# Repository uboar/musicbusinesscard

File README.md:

# musicbusinesscard
 
詳細→https://uboar.hatenablog.com/entry/2020/05/02/111120

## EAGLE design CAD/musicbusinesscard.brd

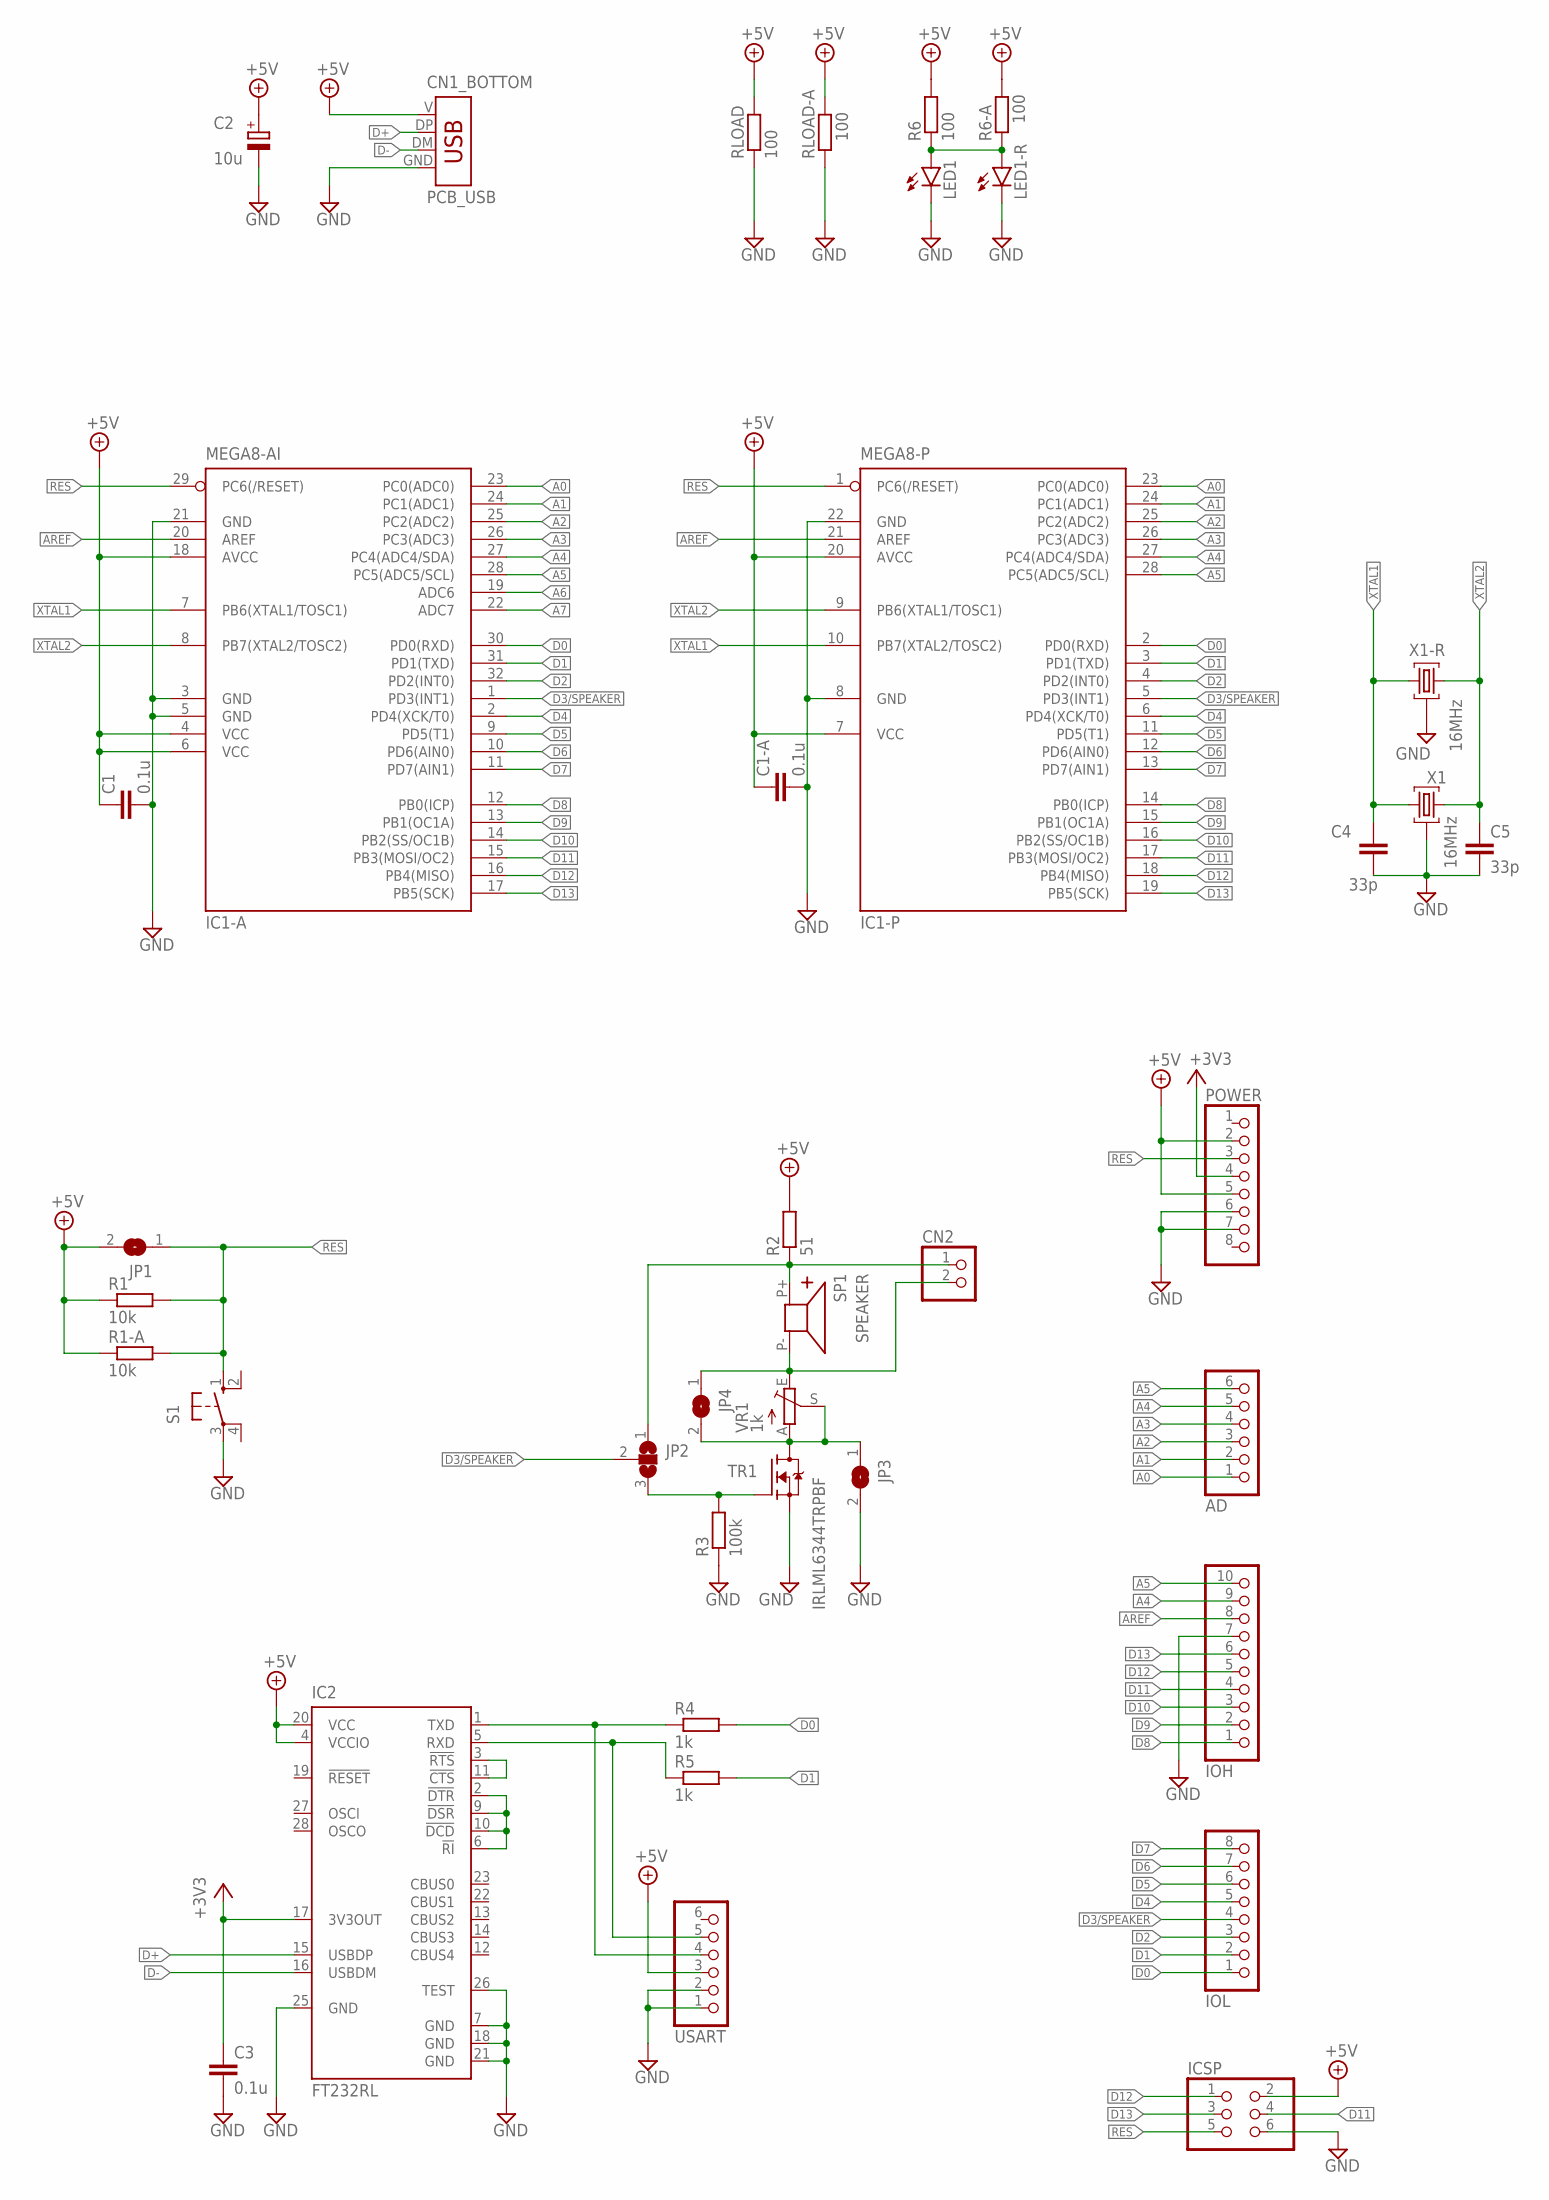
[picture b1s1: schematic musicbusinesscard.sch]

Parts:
AD: PINHD-1X6; 1X06
C1, C3: 0.1u; C3216
C1-A: 0.1u; C050-024X044
C2: 10u; TT2D5
C4, C5: 33p; C050-024X044
CN1_BOTTOM: PCB_USB
CN2: PINHD-1X2; 1X02
IC1-A: MEGA8-AI; TQFP32-08
IC1-P: MEGA8-P; DIL28-3
IC2: FT232RL; SSOP28
ICSP: PINHD-2X3; 2X03
IOH: PINHD-1X10; 1X10
IOL: PINHD-1X8; 1X08
JP1, JP3, JP4: SJ
JP2: SJ2W; SJ_2
LED1: LEDCHIPLED_1206; CHIPLED_1206
LED1-R: LED3MM
POWER: PINHD-1X8; 1X08
R1: 10k; R3216
R1-A: 10k; 0207/10
R2: 51; R3216
R3: 100k; R3216
R4, R5: 1k; R3216
R6: 100; R3216
R6-A: 100; 0207/10
RLOAD: 100; R3216
RLOAD-A: 100; 0207/10
S1: 10-XX; B3F-10XX
SP1: SPEAKER
TR1: IRLML6344TRPBF; SOT23
USART: PINHD-1X6; 1X06
VR1: 1k; B25P
X1: 16MHz; XTAL_MURATA
X1-R: 16MHz; HC49U

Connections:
+3V3: C3.1, IC2.17 (3V3OUT), POWER.4
+5V: C1.1, C1-A.1, C2.+, CN1_BOTTOM.V (1), IC1-A.4 (VCC), IC1-A.6 (VCC), IC1-A.18 (AVCC), IC1-P.7 (VCC), IC1-P.20 (AVCC), IC2.4 (VCCIO), IC2.20 (VCC), ICSP.2, JP1.2, POWER.2, POWER.5, R1.1, R1-A.1, R2.2, R6.2, R6-A.2, RLOAD.2, RLOAD-A.2, USART.3
A0: AD.1, IC1-A.23 (PC0(ADC0)), IC1-P.23 (PC0(ADC0))
A1: AD.2, IC1-A.24 (PC1(ADC1)), IC1-P.24 (PC1(ADC1))
A2: AD.3, IC1-A.25 (PC2(ADC2)), IC1-P.25 (PC2(ADC2))
A3: AD.4, IC1-A.26 (PC3(ADC3)), IC1-P.26 (PC3(ADC3))
A4: AD.5, IC1-A.27 (PC4(ADC4/SDA)), IC1-P.27 (PC4(ADC4/SDA)), IOH.9
A5: AD.6, IC1-A.28 (PC5(ADC5/SCL)), IC1-P.28 (PC5(ADC5/SCL)), IOH.10
A6: IC1-A.19 (ADC6)
A7: IC1-A.22 (ADC7)
AREF: IC1-A.20 (AREF), IC1-P.21 (AREF), IOH.8
D0: IC1-A.30 (PD0(RXD)), IC1-P.2 (PD0(RXD)), IOL.1, R4.2
D1: IC1-A.31 (PD1(TXD)), IC1-P.3 (PD1(TXD)), IOL.2, R5.2
D2: IC1-A.32 (PD2(INT0)), IC1-P.4 (PD2(INT0)), IOL.3
D3/SPEAKER: IC1-A.1 (PD3(INT1)), IC1-P.5 (PD3(INT1)), IOL.4, JP2.2
D4: IC1-A.2 (PD4(XCK/T0)), IC1-P.6 (PD4(XCK/T0)), IOL.5
D5: IC1-A.9 (PD5(T1)), IC1-P.11 (PD5(T1)), IOL.6
D6: IC1-A.10 (PD6(AIN0)), IC1-P.12 (PD6(AIN0)), IOL.7
D7: IC1-A.11 (PD7(AIN1)), IC1-P.13 (PD7(AIN1)), IOL.8
D8: IC1-A.12 (PB0(ICP)), IC1-P.14 (PB0(ICP)), IOH.1
D9: IC1-A.13 (PB1(OC1A)), IC1-P.15 (PB1(OC1A)), IOH.2
D10: IC1-A.14 (PB2(SS/OC1B)), IC1-P.16 (PB2(SS/OC1B)), IOH.3
D11: IC1-A.15 (PB3(MOSI/OC2)), IC1-P.17 (PB3(MOSI/OC2)), ICSP.4, IOH.4
D12: IC1-A.16 (PB4(MISO)), IC1-P.18 (PB4(MISO)), ICSP.1, IOH.5
D13: IC1-A.17 (PB5(SCK)), IC1-P.19 (PB5(SCK)), ICSP.3, IOH.6
D+: CN1_BOTTOM.DP (2), IC2.15 (USBDP)
D-: CN1_BOTTOM.DM (3), IC2.16 (USBDM)
GND: C1.2, C1-A.2, C2.-, C3.2, C4.2, C5.2, CN1_BOTTOM.GND (4), IC1-A.3 (GND), IC1-A.5 (GND), IC1-A.21 (GND), IC1-P.8 (GND), IC1-P.22 (GND), IC2.7 (GND), IC2.18 (GND), IC2.21 (GND), IC2.25 (GND), IC2.26 (TEST), ICSP.6, IOH.7, JP3.2, LED1.C, LED1-R.K (C), POWER.6, POWER.7, R3.1, RLOAD.1, RLOAD-A.1, S1.3, TR1.2 (S), USART.1, USART.2, X1.2, X1-R.2
unnamed: JP2.3, R3.2, TR1.1 (G)
unnamed: CN2.2, JP4.1, SP1.P- (2), VR1.E
unnamed: CN2.1, JP2.1, R2.1, SP1.P+ (1)
unnamed: JP3.1, JP4.2, TR1.3 (D), VR1.A, VR1.S
unnamed: IC2.2 (!DTR), IC2.6 (!RI), IC2.9 (!DSR), IC2.10 (!DCD)
unnamed: IC2.3 (!RTS), IC2.11 (!CTS)
unnamed: IC2.1 (TXD), R4.1, USART.4
unnamed: IC2.5 (RXD), R5.1, USART.5
unnamed: LED1.A, LED1-R.A, R6.1, R6-A.1
RES: IC1-A.29 (PC6(/RESET)), IC1-P.1 (PC6(/RESET)), ICSP.5, JP1.1, POWER.3, R1.2, R1-A.2, S1.1 (S)
XTAL1: C4.1, IC1-A.7 (PB6(XTAL1/TOSC1)), IC1-P.10 (PB7(XTAL2/TOSC2)), X1.1, X1-R.1
XTAL2: C5.1, IC1-A.8 (PB7(XTAL2/TOSC2)), IC1-P.9 (PB6(XTAL1/TOSC1)), X1.3, X1-R.3

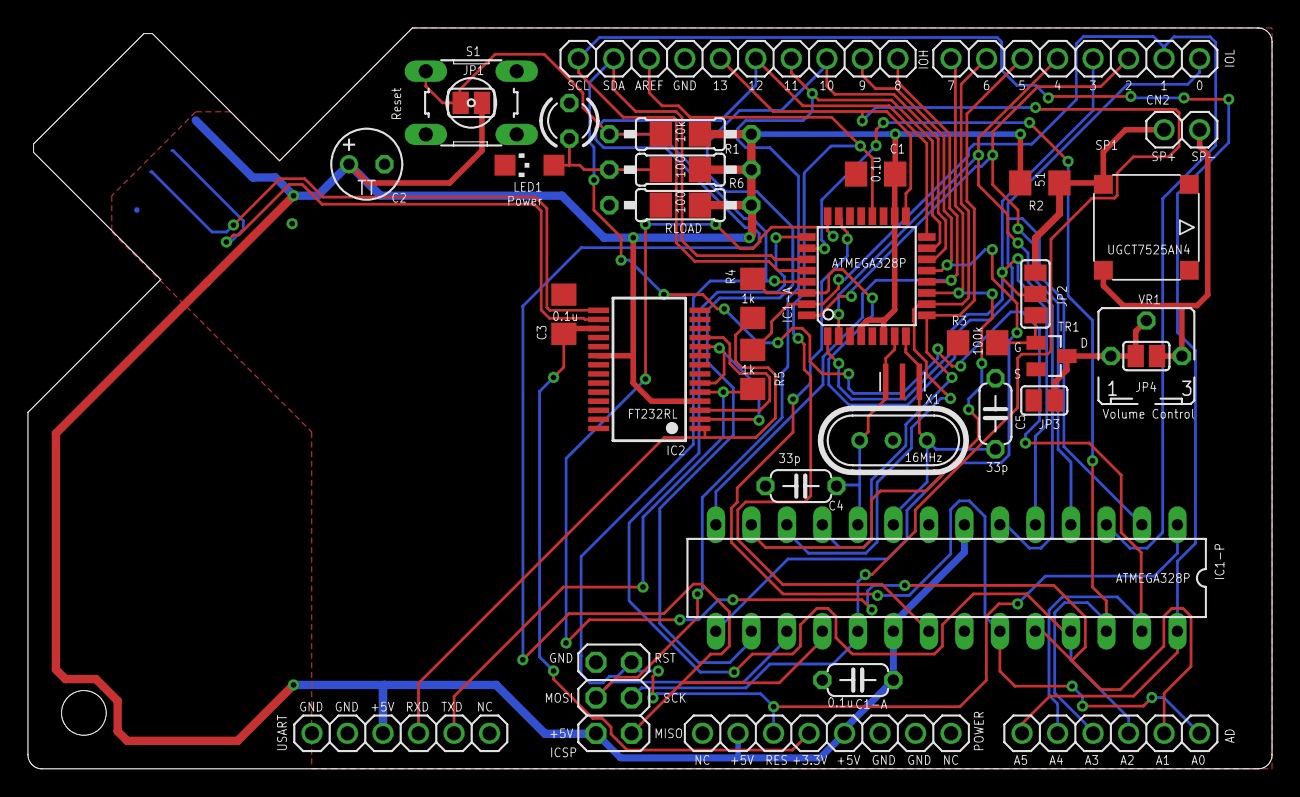
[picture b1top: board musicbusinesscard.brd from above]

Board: 2 copper layers, 89.0 x 53.0 mm, 39 parts (1 on the bottom side), 38 nets.

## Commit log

2020-05-02 Create musicbusinesscard.ino
    Arduinoソース
2020-05-02 readme update
